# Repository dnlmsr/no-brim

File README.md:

# no-brim

## Descrizione
Il progetto no-brim (no Barbaric Resizing Is Mandatory) è il progetto di una macchina in grado di realizzare lunghezze di tubi in PVC o altri materiali plastici definite dall'utente. L'intero sistema è basato sulla piattaforma open source Arduino MEGA che gestisce tutti gli input e gli output e le interazioni con l'utente.
## Autori
* [Daniele Moser](mailto:dnlmsr0@gmail.com)
* [Francesco Maraner](mailto:francesco.maraner@marconirovereto.it)
* [Michele Mattè](mailto:michele.matte@marconirovereto.it)

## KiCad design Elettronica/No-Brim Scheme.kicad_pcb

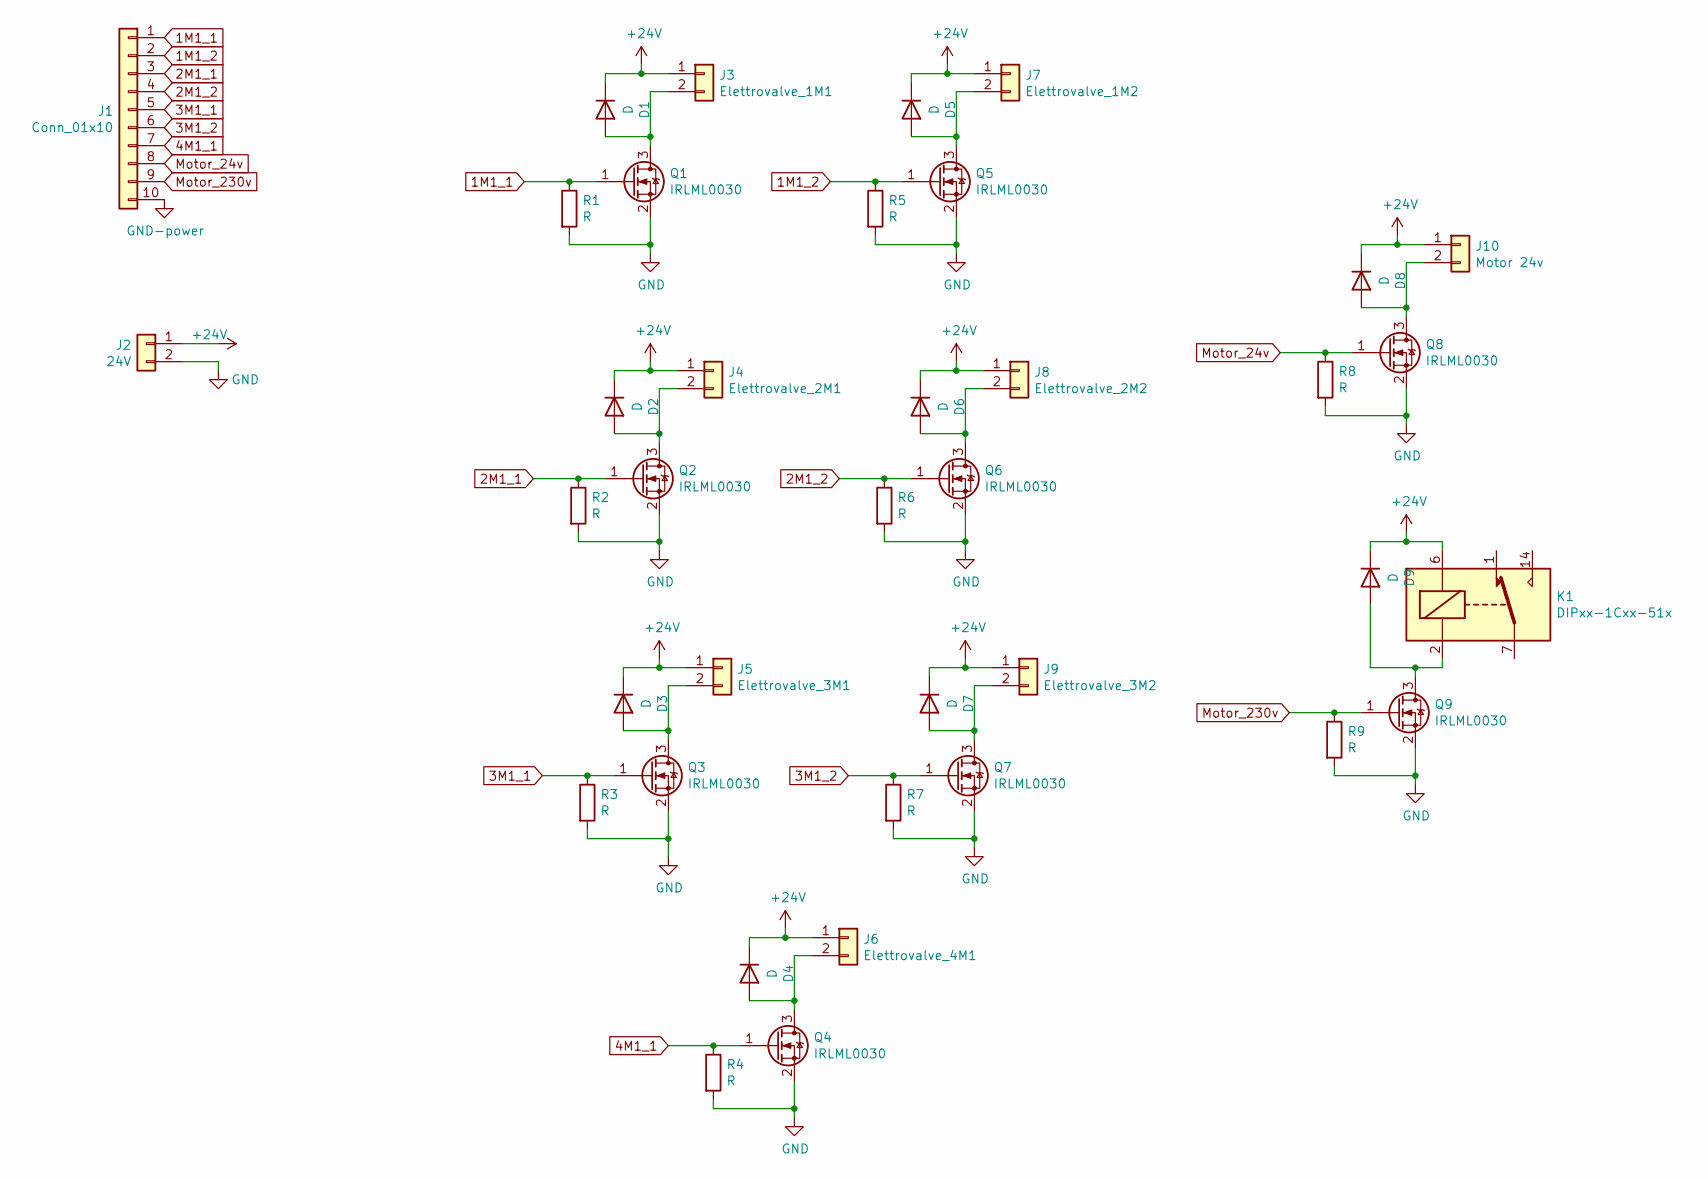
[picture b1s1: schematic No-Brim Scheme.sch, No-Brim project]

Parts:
D1, D2, D3, D4, D5, D6, D7, D8, D9: D; D_2010_5025Metric_Pad1.52x2.65mm_HandSolder
J1: Conn_01x10; PinSocket_1x10_P2.54mm_Vertical
J2: 24V; PinSocket_1x02_P2.00mm_Vertical
J3: Elettrovalve_1M1; PinSocket_1x02_P2.54mm_Vertical
J4: Elettrovalve_2M1; PinSocket_1x02_P2.54mm_Vertical
J5: Elettrovalve_3M1; PinSocket_1x02_P2.54mm_Vertical
J6: Elettrovalve_4M1; PinSocket_1x02_P2.54mm_Vertical
J7: Elettrovalve_1M2; PinSocket_1x02_P2.54mm_Vertical
J8: Elettrovalve_2M2; PinSocket_1x02_P2.54mm_Vertical
J9: Elettrovalve_3M2; PinSocket_1x02_P2.54mm_Vertical
J10: Motor 24v; PinSocket_1x02_P2.54mm_Vertical
K1: DIPxx-1Cxx-51x; Relay_StandexMeder_DIP_LowProfile
Q1, Q2, Q3, Q4, Q5, Q6, Q7, Q8, Q9: IRLML0030; SOT-23
R1, R2, R3, R4, R5, R6, R7, R8, R9: R; R_1206_3216Metric_Pad1.42x1.75mm_HandSolder

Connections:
1M1_1: J1.1, Q1.1 (G), R1.1
1M1_2: J1.2, Q5.1 (G), R5.1
2M1_1: J1.3, Q2.1 (G), R2.1
2M1_2: J1.4, Q6.1 (G), R6.1
3M1_1: J1.5, Q3.1 (G), R3.1
3M1_2: J1.6, Q7.1 (G), R7.1
4M1_1: J1.7, Q4.1 (G), R4.1
+24V: D1.1 (K), D2.1 (K), D3.1 (K), D4.1 (K), D5.1 (K), D6.1 (K), D7.1 (K), D8.1 (K), D9.1 (K), J2.1, J3.1, J4.1, J5.1, J6.1, J7.1, J8.1, J9.1, J10.1, K1.6
Motor_24v: J1.8, Q8.1 (G), R8.1
Motor_230v: J1.9, Q9.1 (G), R9.1
unnamed: D1.2 (A), J3.2, Q1.3 (D)
unnamed: D2.2 (A), J4.2, Q2.3 (D)
unnamed: D3.2 (A), J5.2, Q3.3 (D)
unnamed: D4.2 (A), J6.2, Q4.3 (D)
unnamed: D5.2 (A), J7.2, Q5.3 (D)
unnamed: D6.2 (A), J8.2, Q6.3 (D)
unnamed: D7.2 (A), J9.2, Q7.3 (D)
unnamed: D8.2 (A), J10.2, Q8.3 (D)
unnamed: D9.2 (A), K1.2, Q9.3 (D)
unnamed: K1.7, K1.8

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
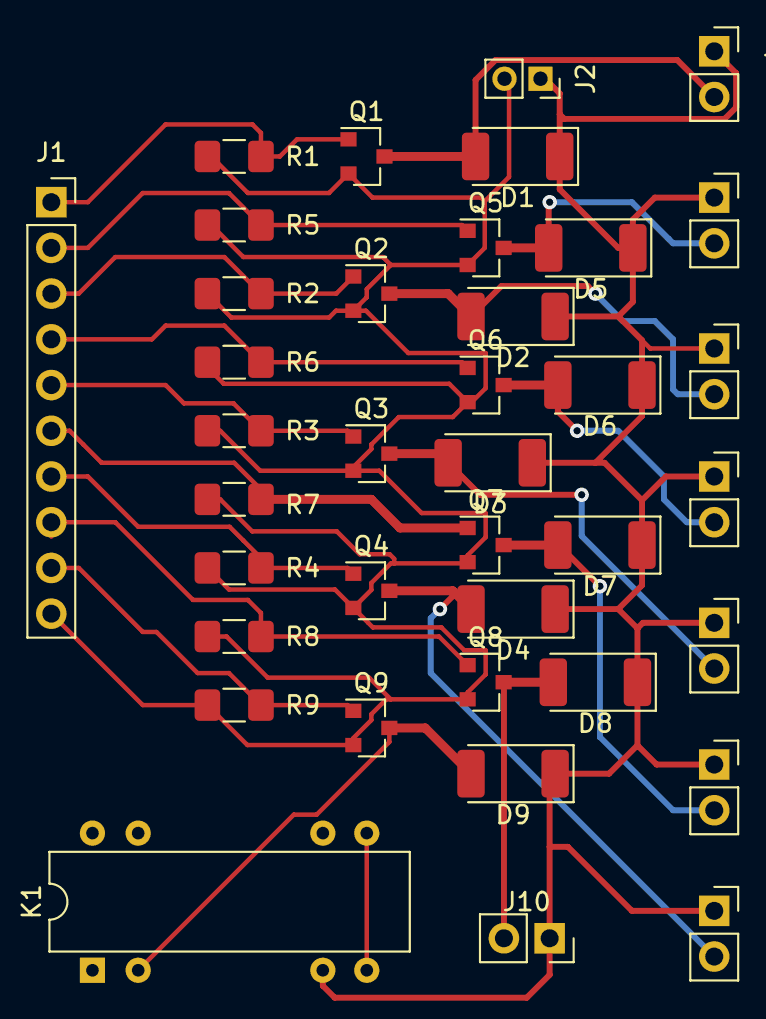
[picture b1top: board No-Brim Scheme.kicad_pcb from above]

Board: 2 copper layers, 38 parts (0 on the bottom side), 21 nets.

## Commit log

2020-05-29 prima parte macchina no brim
2020-05-29 Organizzata repository
2020-05-30 Ricreato progetto
2020-05-30 Nuovo schizzo Trasporto
2020-05-30 Modificato gitingore e README
2020-06-01 Definita struttura documentazione
2020-06-01 Quasi completato trasporto, iniziata la parte di taglio
2020-06-03 Lista componenti principali
2020-06-03 Modifiche parte trasporto
2020-06-05 Modifiche trasmissione e telaietto
2020-06-10 Create task e scheduler
2020-06-10 Schema 10/6
2020-06-11 Aggiunte Eletrovalvole mancanti
2020-06-12 Aggiunta pistone salita lama e modifiche varie
2020-06-15 Integrazione funzionalità PID
2020-06-15 Modificato README
2020-06-15 Aggiustata BOM
2020-06-16 Modifiche allo schema e pcb recuperato(16/6)
2020-06-16 PCB completato da revisionare(16/6)
2020-06-16 Progetto quasi finito
2020-06-19 Modificato PID
2020-06-19 Definito sistema a stati
2020-06-19 Aggiunto Asse lineare e motore annesso
2020-06-19 Commentato codice
2020-06-19 Implementato movimento data misura del tubo
2020-06-21 Alimentazione 230v & 24v
2020-06-21 Modifiche alla scaletta + Disegni quadro spostati
2020-06-21 Aggiustati commenti
2020-06-22 Parte Inventor finita, primi PDF e documentazione meccanica
2020-06-24 Modificata BOM
2020-06-25 Modificata documentazione di meccanica
2020-06-25 25/6
2020-06-26 Creato simulatore asse lineare
2020-06-26 Aggiunta parte elettronica fino a 25/6
2020-06-26 2 pdf pistoni
2020-06-26 Aggiunta parte elettronica fino a 26/6
2020-06-26 Modificata documentazione elettronica e prima parte programma
2020-06-29 Modificata parte elettronica
2020-06-29 Aggiunte immagini sezione meccanica
2020-06-29 Aggiunta piccola parte su sviluppi futuri
2020-06-29 Aggiustato ciclogramma
2020-06-29 Aggiunta documentazione sistemi
2020-07-01 Indroduzione aggiunta + Sviluppo futuro rivisto
2020-07-01 Introduzione aggiunta + Sviluppo futuro rivisto
2020-07-01 Aggiunte tavole e crediti
2020-07-01 Aggiustata tabella puleggie
2020-07-01 Aggiunto sviluppo futuro
2020-07-01 Ultime modifiche documentazione e compilazione pdf
